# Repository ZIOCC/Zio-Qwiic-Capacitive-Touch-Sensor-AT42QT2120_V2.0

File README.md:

## Zio Qwiic Capacitive Touch Sensor AT42QT2120 V2.0

This product can be available for purchase [here](https://www.smart-prototyping.com/Zio-Qwiic-Capacitive-Touch-Sensor-Module-AT42QT2120).

### Description

This is a Qwiic version of the touch sensor based on the AT42QT2120 sensor. It can sense up to 12 keys, dependent on mode. Three of the keys can be used as sense channels for a slider or wheel, and 9 standard touch keys.

The Touch Wheel in this sensor is unique and different from other similar looking wheel sensors in terms of its added functionality. It can also be applied to create applications that need volume adjustment, light brightness, or wheel lights.

We’ve prepared the touch wheel and the keyboard for you and also included the source PCB file on our GitHub page for easy customization.

### Specifications

* IC :  AT42QT2120 & PCF8574T
* Default I2C Address: 0x1c & 0x23
* Operation Voltage: 3.3V
* Main board 
    - Dimension: 46.7 x 46.7mm
    - Weight: 7.6g
* Wheel touchpad: 
    - 0-255 ADC output, 
    - Dimension: 33.8mm diameter
    - Weight: 4.3g
* Keyboard, 
    - 9 keys, from key 4 to key 11
    - Dimension: 66.9 x 99.8mm 
    - Weight: 22.3g

###### About Zio
> Zio is a new line of open sourced, compact, and grid layout boards, fully integrated for Arduino and Qwiic ecosystem. Designed ideally for wearables, robotics, small-space limitations or other on the go projects. Check out other awesome Zio products [here](https://www.smart-prototyping.com/Zio).

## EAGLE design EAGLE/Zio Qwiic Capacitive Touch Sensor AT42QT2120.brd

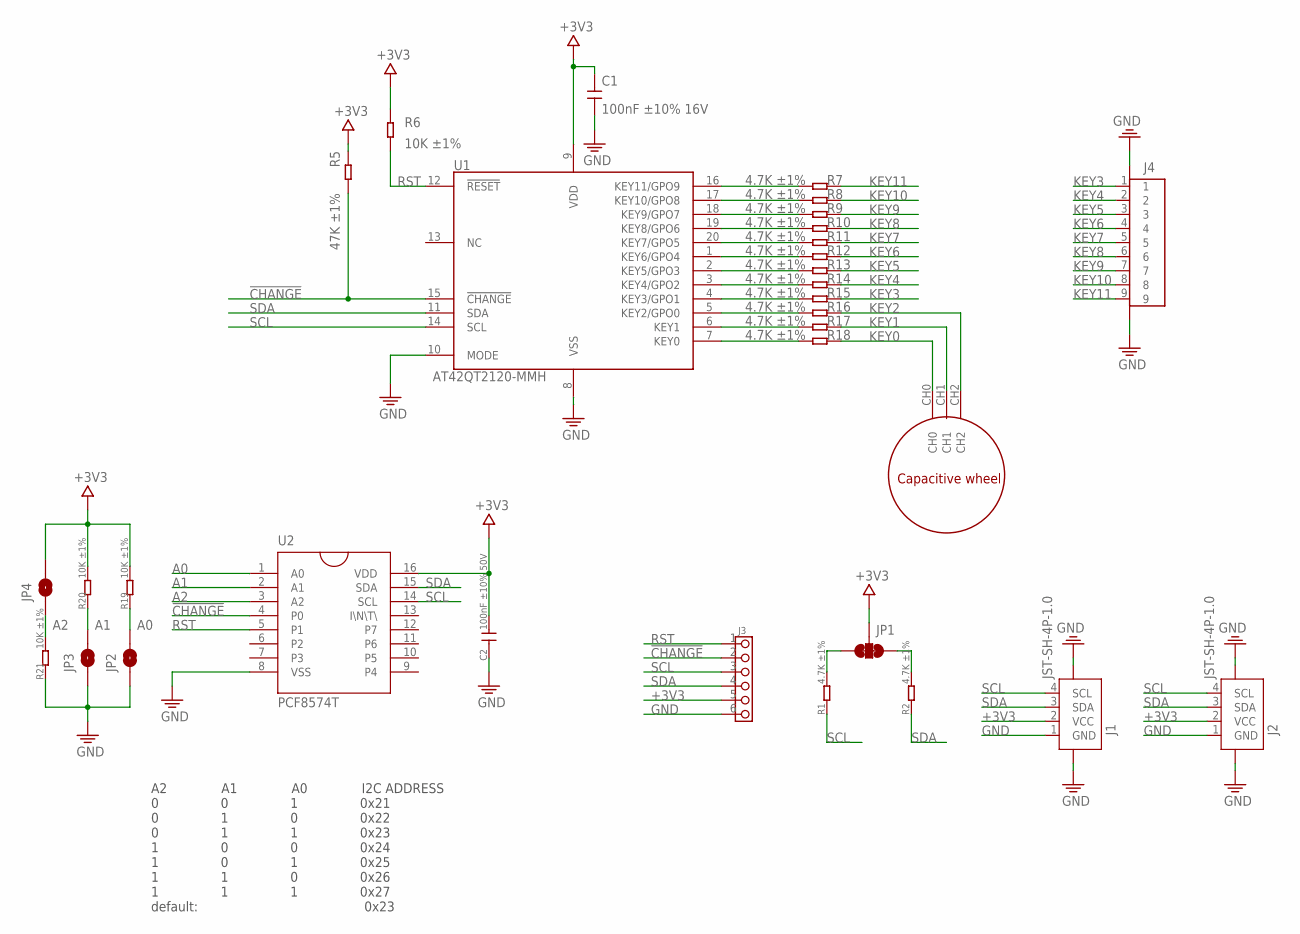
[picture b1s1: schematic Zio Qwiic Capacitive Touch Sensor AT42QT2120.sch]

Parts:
C1: 100nF ±10% 16V; C0603; VOLTAGE 25V
C2: 100nF ±10% 50V; C0603
J1, J2: JST-SH-4P-1.0; JST-SH-4P
J3: HEADER-6P-60/35MIL; 6P-2.54-60/35MIL
J4: FPC-0.5-9P; FPC-0.5-9P_UP
JP1: SMT-JUMPER_3_2-NC_TRACE
JP2, JP3, JP4: JUMPER-SMT_2_NC_PASTE_NOCREM; SMT-JUMPER_2_NC_PASTE_SILK_NOCREM
R1, R2: 4.7K ±1%; R0603
R5: 47K ±1%; R0603
R6, R19, R20, R21: 10K ±1%; R0603
R7, R8, R9, R10, R11, R12, R13, R14, R15, R16, R17, R18: 4.7K ±1%; R0402
U1: AT42QT2120-MMH; QFN45P300X300X85-21N
U2: PCF8574T; SO16-W
U3: QTWHEEL_MODULE; QTWHEELMODULE

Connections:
!CHANGE: J3.2, R5.1, U1.15 (!CHANGE), U2.4 (P0)
+3V3: C1.1, C2.2, J1.2 (VCC), J2.2 (VCC), J3.5, JP1.2, JP4.2, R5.2, R6.2, R19.2, R20.2, U1.9 (VDD), U2.16 (VDD)
A0: JP2.2, R19.1, U2.1 (A0)
A1: JP3.2, R20.1, U2.2 (A1)
A2: JP4.1, R21.2, U2.3 (A2)
GND: C1.2, C2.1, J1.1 (GND), J1.NC1 (5), J1.NC2 (6), J2.1 (GND), J2.NC1 (5), J2.NC2 (6), J3.6, J4.11 (G2), JP2.1, JP3.1, R21.1, U1.8 (VSS), U1.10 (MODE), U2.8 (VSS)
KEY0: R18.1, U3.CH0
KEY1: R17.1, U3.CH1
KEY2: R16.1, U3.CH2
KEY3: J4.1, R15.1
KEY4: J4.2, R14.1
KEY5: J4.3, R13.1
KEY6: J4.4, R12.1
KEY7: J4.5, R11.1
KEY8: J4.6, R10.1
KEY9: J4.7, R9.1
KEY10: J4.8, R8.1
KEY11: J4.9, R7.1
unnamed: JP1.1, R2.2
unnamed: JP1.3, R1.2
unnamed: R7.2, U1.16 (KEY11/GPO9)
unnamed: R8.2, U1.17 (KEY10/GPO8)
unnamed: R9.2, U1.18 (KEY9/GPO7)
unnamed: R10.2, U1.19 (KEY8/GPO6)
unnamed: R11.2, U1.20 (KEY7/GPO5)
unnamed: R12.2, U1.1 (KEY6/GPO4)
unnamed: R13.2, U1.2 (KEY5/GPO3)
unnamed: R14.2, U1.3 (KEY4/GPO2)
unnamed: R15.2, U1.4 (KEY3/GPO1)
unnamed: R16.2, U1.5 (KEY2/GPO0)
unnamed: R17.2, U1.6 (KEY1)
unnamed: R18.2, U1.7 (KEY0)
RST: J3.1, R6.1, U1.12 (!RESET), U2.5 (P1)
SCL: J1.4 (SCL), J2.4 (SCL), J3.3, R1.1, U1.14 (SCL), U2.14 (SCL)
SDA: J1.3 (SDA), J2.3 (SDA), J3.4, R2.1, U1.11 (SDA), U2.15 (SDA)

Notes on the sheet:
A2 A1 A0 I2C ADDRESS 0 0 1 0x21 0 1 0 0x22 0 1 1 0x23 1 0 0 0x24 1 0 1 0x25 1 1 0 0x26 1 1 1 0x27 default: 0x23

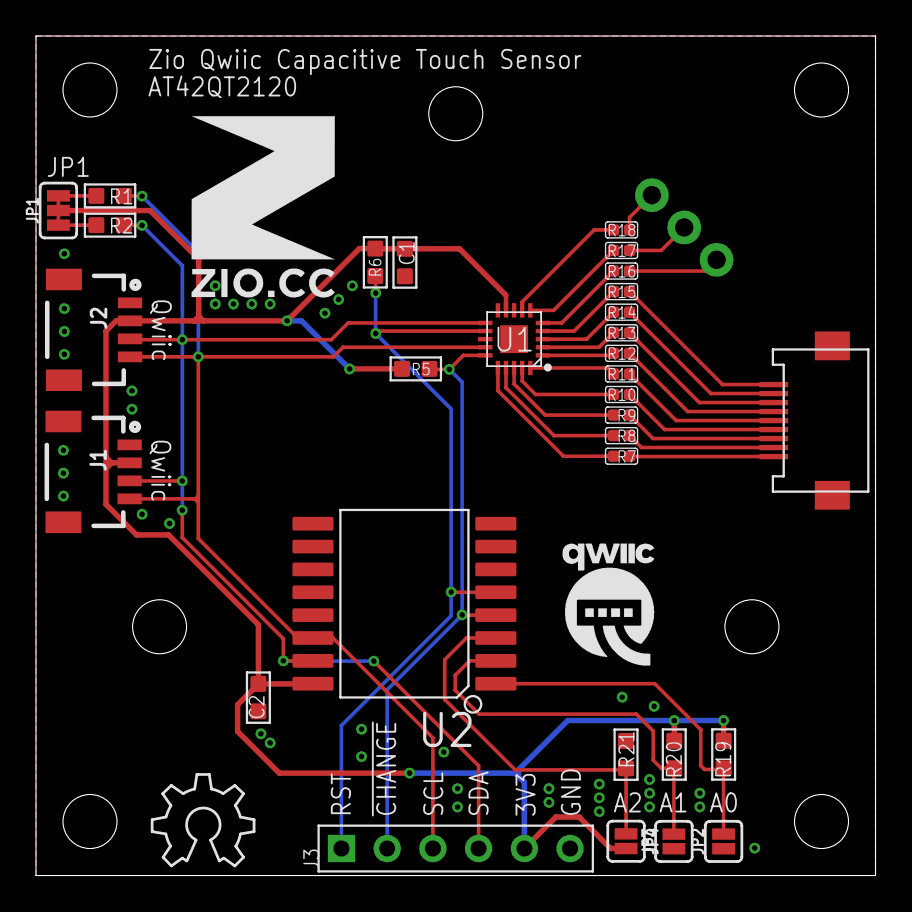
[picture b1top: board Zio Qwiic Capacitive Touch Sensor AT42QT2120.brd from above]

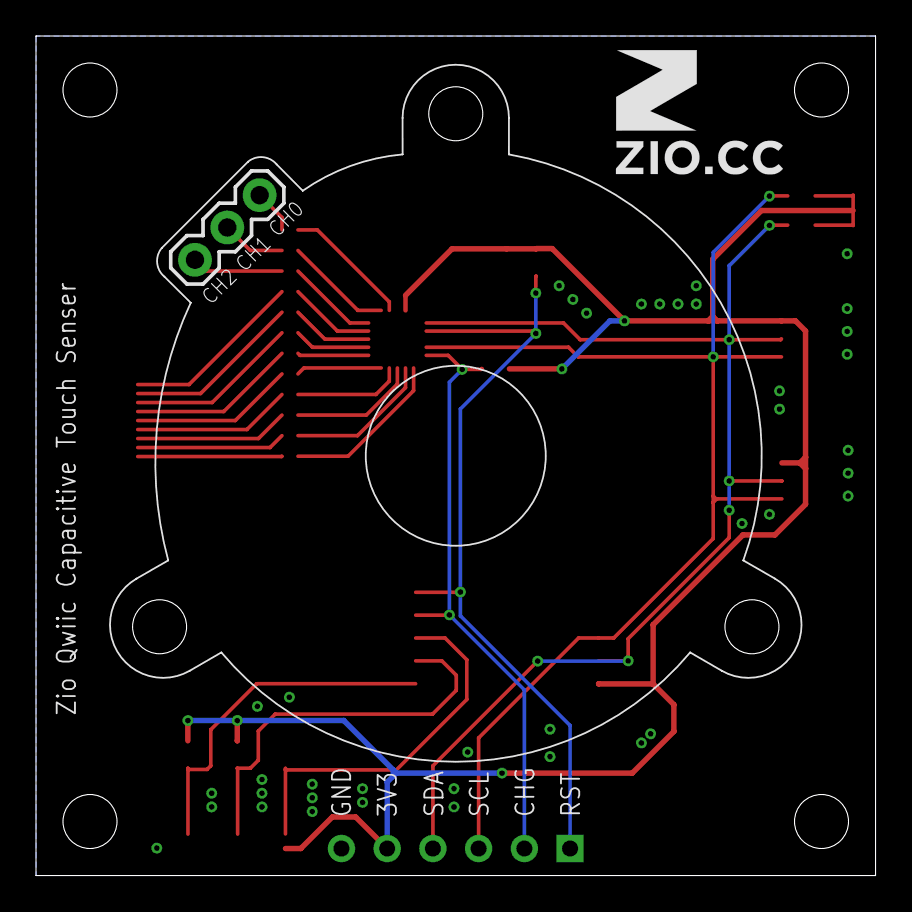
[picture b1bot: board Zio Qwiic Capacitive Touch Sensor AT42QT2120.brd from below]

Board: 2 copper layers, 46.6 x 46.6 mm, 36 parts (2 on the bottom side), 35 nets.

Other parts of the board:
U$1: 7MM
U$2: 10MM
U$3: OSHW_6X200_NOTEXT
U$4: QWIIC-LOGO-MEDIUM
